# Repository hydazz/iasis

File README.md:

# iasis

Iasis is a five-port USB-C hub for restoring Apple devices. It can put Macs into DFU mode without the keyboard sequence. The host runs the restores on macOS, Linux or Windows. The same ports connect ordinary USB peripherals.

The hardware is a prototype.

## Hardware

The main board has a USB-C power input and a charging supply for each target port. A power supply on that input runs the hub and charges the targets. Without one, the host port runs the hub, and a USB-C host advertising 1.5 A or 3 A also powers the targets.

The optional [CM5 carrier](hardware/boards/cm5/README.md) plugs into the main board and houses a Compute Module 5, NVMe storage and Ethernet. The [printed case](hardware/case/README.md) holds the main board alone or with the carrier, with plain or OLED lids.

See the [main board](hardware/boards/iasis/README.md) for fabrication files and ordering settings.

## Software

| Part                                    | Role                                       |
| --------------------------------------- | ------------------------------------------ |
| [IasisOS](crates/firmware/README.md)    | Firmware on the hub's RP2354               |
| [`iasisd`](#host-agent)                 | Host agent: follows hubs and runs restores |
| `iasis`                                 | Command-line control of hubs and the agent |
| [Iasis for macOS](apps/macos/README.md) | Menu bar app, with the host tools inside   |

They share one version and are released together.

## Build

Install [mise](https://mise.jdx.dev/) and, for hardware work, KiCad 10 with its standard libraries. Run from the repository root:

```sh
mise install
mise run deps
mise run host:build
```

The host tools are `target/release/iasis` for hub control and `target/release/iasisd`, the [host agent](#host-agent). Keep `iasis-gateway` beside both. The agent needs read/write access to the management USB device. On Linux, the [Debian package](crates/iasis/README.md#debian-package) installs them with that access, and on Windows the [installer](crates/iasis/README.md#windows-installer).

The build compiles the restore engine's C libraries from source. Install their build tools first: on macOS, the Xcode command line tools and `brew install autoconf automake libtool pkg-config cmake`; on Debian or Ubuntu, `build-essential git autoconf automake libtool pkg-config cmake libpcap-dev libusb-1.0-0-dev`; on Windows, `mise bootstrap` (MSYS2 and its MINGW64 packages) with rustup's default host set to `x86_64-pc-windows-gnu`, building from MSYS2's MINGW64 shell.

| Task               | Output                                                            |
| ------------------ | ----------------------------------------------------------------- |
| `mise run build`   | Host tools, IasisOS, case STLs, board STEPs and fabrication files |
| `mise run lint`    | Rust, Python, workflow and KiCad checks                           |
| `mise run test`    | Software, placement-conversion and case-fit tests                 |
| `mise run preview` | Board and case images                                             |
| `mise run format`  | Formatted sources and configuration                               |

Builds, checks and previews are separate tasks. Python tools share the root `.venv`; `mise install` also installs the Lefthook hooks.

## Use

Connect the host and charged targets. Ports are numbered 1–5, starting at the dot on the case.

```sh
target/release/iasis
target/release/iasis list
target/release/iasis --serial 0123456789abcdef rename "Bench A"
target/release/iasis --hub "Bench A" dfu 1
target/release/iasis --hub "Bench A" ports --watch
```

`iasis` alone lists every hub and its ports; `iasis watch` keeps the list current. It works through the [host agent](#host-agent), which must be running. With one hub attached, commands act on it; with several, select one by name or by the serial from `iasis list`. Names match without case, can contain spaces and punctuation, and fit the OLED’s 16 printable ASCII characters. If two hubs share a name, select by serial. An empty name clears the label. Use `ports --watch` to see the USB mode, identity and link (none, USB 2 or USB 3) on each port. If a Mac acknowledges the DFU request and then disappears from USB, check the data cable and the Mac’s [DFU socket](https://support.apple.com/en-us/120694). A locked Mac laptop withholds USB data from an accessory it has not allowed until someone unlocks it and allows it ([Apple](https://support.apple.com/en-us/102282)); until then its port shows power and no link, and DFU still works.

The button selects targets with a tap and acts on them with a hold, with or without an OLED.

| Button           | Status light | Result                                                |
| ---------------- | ------------ | ----------------------------------------------------- |
| Tap              |              | Select All, then each attached port in turn           |
| Hold and release | Blue         | DFU                                                   |
|                  | Amber        | Reboot                                                |
|                  | Purple       | Ask the waiting host to prepare a [restore](#restore) |
| Keep holding     | Normal       | Nothing is sent                                       |

A hold steps through the actions the selected targets take, in this order: the first after half a second, each next one 1.5 seconds later. DFU and Reboot are offered only where a target lists them, and DFU only on a port that carries the target's DFU USB. On a Mac that is its DFU port; its other ports take Reboot.

Port lights outside the selection dim. While the button is held, only the ports the action will reach stay bright. An emptied port stays selected for 30 seconds so a replacement target takes its place.

After a DFU the port pulses blue. It turns steady blue once a host sees the target in DFU, which needs the [host agent](#host-agent). The [light table](crates/firmware/README.md#controls-and-status) lists every colour.

A steady white port light marks a device Iasis cannot act on, such as a USB peripheral or a laptop. It can use USB normally. DFU leaves target data intact and works with Apple Configurator. `power <port> off` disables a port. `power <port> on` enables it and retries a fault. The selected hub stores its name and light brightness in flash.

With Default USB power, including an A-to-C cable, the target ports stay off until a power supply is connected. A USB-C host advertising 1.5 A or 3 A can power the ports directly. They share the available current. Connect external power if the targets draw more during recovery. See the [firmware power table](crates/firmware/README.md#port-power) for the limits.

### Host agent

`iasisd` attends every connected hub and needs no arguments:

```sh
target/release/iasisd
```

While the agent is running:

- It tells each hub which USB mode its targets are in, so a port light turns steady blue when its target really is in DFU, however it got there.
- It keeps the [restore images](#images) and fetches the ones it lacks.
- It runs the restores that a hub's button or a client asks for.
- On Linux and macOS, it can share an internet connection with attached devices over USB.

The status light is green and the OLED shows a USB symbol while a host is attached. One host holds a hub at a time, and on it only the agent opens the hub; `iasis` and the Mac app are its clients, and other clients use its [local socket](crates/api/README.md). Without the agent, `iasis` says how to start it.

On Linux, the [Debian package](crates/iasis/README.md#debian-package) runs the agent at boot for the person signed in at the computer and members of the `iasis` group. On Windows, the [installer](crates/iasis/README.md#windows-installer) runs it at boot for Administrators and the person signed in at the computer. On macOS, the [menu bar app](apps/macos/README.md) shows the same hubs and ports, sends the same actions and runs the agent it carries while you are logged in. To run your own build in the background, turn Iasis off under Background App Activity in Login Items & Extensions, then prefix the command with `launchctl submit -l local.iasisd --`. With `IASIS_HOME` set to a directory, the agent keeps its files and socket there, and `iasis` with the same `IASIS_HOME` talks to it.

### USB Internet Sharing

On Linux or macOS, use the CLI. The Mac app also has **Share internet over USB** in Settings > General.

```sh
iasis sharing on
iasis sharing       # show the setting and ports being served
iasis sharing off
```

A directly attached Apple device that offers USB Ethernet can use the host’s internet connection over its charging and restore cable. Sharing follows the host’s routing and resumes when a device restarts. The OLED shows a network symbol while the agent serves at least one port on that hub.

On Linux, a Mac is served once the kernel’s `cdc_ncm` driver lists its USB ID: from Linux 7.2 for the M5 MacBook Air (`linux-oem-26.04b` on Ubuntu 26.04) and 7.4 for the M1 MacBook Air. iPhones and iPads won’t be served until Debian and Ubuntu ship a usbmuxd newer than 1.1.1.

Windows can't share: Microsoft's NCM driver fails on a Mac's USB Ethernet, and Apple's Windows driver keeps iPhones and iPads from offering theirs.

A Mac with no USB device of its own while it runs, such as the MacBook Neo, reaches the host only through Apple Debug USB. The agent turns it on when such a Mac's port shows nothing on USB, and a DFU or restore through Iasis keeps it on into the restored system. macOS and the Linux agent present the Mac behind it, Linux without `cdc_ncm`, while the Mac is awake.

Setup Assistant can use this connection for Automated Device Enrollment. See the [Mac app guide](apps/macos/README.md#usb-internet-sharing) for host permissions.

### Images

The agent holds IPSW archives. One archive restores every model its manifest names: a macOS image restores every Mac that release supports, and an iPadOS or iOS image a few related models. Archives for different models can share a version and build number.

A restore asks what Apple signs for each device before it chooses an image:

- With no image that fits, it downloads the newest release.
- With an image that is the newest release, or newer, it uses it.
- With an older image Apple still signs, it uses that one, or downloads the newest with `--latest`. The Mac app asks which.
- An image Apple no longer signs is deleted and the newest release downloaded. Apple signs older macOS releases for a long time and older iOS and iPadOS releases only briefly.
- When the catalog cannot be reached, the newest image that fits is used.

Any release Apple signs can also be downloaded ahead of time. Release listings come from [ipsw.me](https://ipsw.me) and the archives from Apple's servers, checked against their published SHA-256.

```sh
target/release/iasis images                           # each image by name, and any download
target/release/iasis images releases Macmini9,1       # the releases Apple signs for a model
target/release/iasis images fetch Macmini9,1          # download the newest of them
target/release/iasis images fetch Macmini9,1 --build 25G80
target/release/iasis images add /path/to/UniversalMac.ipsw
target/release/iasis images remove UniversalMac_27.2.1_26B131_Restore.ipsw
```

An image stays until it is removed. Removing one that is still downloading stops the download, and removing one a restore is reading takes it out when that restore ends, unless a restore or `images fetch` asks for its release first. A download goes on while a restore waits for it or after `images fetch`; one that no restore waits for any longer stops. An image added from a file is never taken for an unsigned one, since the catalog may not list it. Downloaded images live in the agent's cache directory, `~/Library/Caches/com.hydaz.Iasis` on macOS and `/var/cache/iasis` on Linux, which the system may clear; the agent then downloads an image again when a restore needs it. Images added from a file live in its state directory, `~/Library/Application Support/com.hydaz.Iasis` on macOS and `/var/lib/iasis` on Linux. On macOS, a release Finder has already downloaded to `~/Library/iTunes` is cloned from there instead, once its SHA-256 matches. `images add` sends the archive to the agent, which keeps it once every member's checksum matches. The agent owns both directories: when it starts, it lists any archive it finds there that it did not, once every member's checksum matches, and deletes one that does not. A Mac image is about 26 GB and an iPad image about 11 GB.

While an image is being fetched for a target, its port pulses purple, the OLED labels it `IMG`, and `iasis` shows the percentage.

### Restore

Restores are built into the host tools through [RestoreKit](https://github.com/fcjr/restorekit), for targets in ordinary DFU and Apple Debug USB DFU. On Linux they go through the system usbmuxd. An iPhone or iPad the hub can't signal into DFU, such as one on a Lightning cable, restarts into recovery mode at the host's request and restores from there. It must trust the host: unlock it and tap Trust when it asks, unless its enrollment profile lists the host's [supervision certificate](#supervised-iphones-and-ipads).

```sh
target/release/iasis --serial 0123456789abcdef restore --ports 1,2,3,4,5 --erase
```

**`--erase` erases the selected targets.** The agent runs the restore, and the command follows each port and prints its result as soon as that port ends. The [image store](#images) supplies each target's image.

Each target is its own job, and each restore its own process. A job fetches the target's image before it puts the target into DFU or recovery when this host already knows the target's model; otherwise the target waits there for it. A restore that fails while its target is still in DFU or recovery is started again, up to three times. A target that can’t be prepared, such as an iPad waiting for Trust, ends with the reason on its port while the others restore.

Erased Macs restart into Setup Assistant. Add `--shutdown-macs` to a restore command to power them off after that erase. Revived devices always restart.

To advance Setup Assistant on iPhones and iPads, supply the language and regional format. Add `--enroll` to request Automated Device Enrollment.

```sh
iasis advance-setup --ports 1,2 --language en-AU --locale en_AU
iasis advance-setup --ports 1,2 --language en-AU --locale en_AU --enroll
```

The same options on `iasis restore --erase` run setup after installation. Each device keeps any language or region it has already accepted. The CLI prints the result for each port.

In the Mac app, choose the language, region and enrollment preference in **Settings > Restore**. **Advance Setup** applies them immediately. **Advance Setup After Erase** also applies them to erases started from the app or the hub button.

Advance Setup activates the device if needed. With enrollment enabled, it then requests the assigned management profile. The host needs internet access for activation. The device reaches its enrollment service over Wi-Fi or USB Internet Sharing. If the result says “continue on device”, follow the sign-in or management prompt in Setup Assistant. A “Partially Set Up” prompt also needs a choice on the device.

The host stays out of idle sleep from a target's preparation until its restore ends, while its display can still sleep. On battery, a Windows laptop with Modern Standby drops that hold five minutes after its sleep timeout.

The device inspector shows the requested steps and keeps each outcome. During installation, the restore row shows the current activity, an overall progress bar and an approximate countdown.

Logs and working files go under `restores/` in the agent's cache directory. Allow space for an extracted OS image per worker. Iasis matches each image to the target's chip and board IDs, or to its product type when only a model identifier is available. The restore program checks Apple signing.

On macOS 27.3, Finder opens a window for each Mac, iPad or iPhone that enters DFU or recovery mode. To stop it, turn off **Open Finder for DFU and Recovery** in the app's Settings > General, or run this once as the user running Finder. The preference is undocumented.

```sh
defaults write com.apple.AMPDeviceDiscoveryAgent reveal-devices -bool false
```

To restore the default behaviour, run `defaults delete com.apple.AMPDeviceDiscoveryAgent reveal-devices`.

#### Supervised iPhones and iPads

An iPhone or iPad whose enrollment profile lists the agent's supervision certificate pairs with the host without asking for Trust, so its restores through recovery need no one at the device. Other devices still ask.

The agent makes its identity when it first starts. Export the certificate with Export… in the identity's ⋯ menu, in the Mac app's Settings > Restore, or with `iasis supervision certificate Iasis.cer`, and add it to the devices' Automated Device Enrollment profile as a supervising host certificate. In Intune that is Sync with computers, Allow Apple Configurator by certificate, in the enrollment program token's profile. A device takes the certificate when it enrolls, so an enrolled one needs one erase, with a Trust tap, and enrollment again first.

To back the identity up or give another host the same one, export it with its private key in a password-protected PKCS #12 archive, with Export… in the Mac app or `iasis supervision export Iasis.p12`, and import it with Import… or `iasis supervision import Iasis.p12`. The agent keeps it as `supervision.pem` in its state directory, open to the agent's account alone: mode 600 in a 700 directory on macOS (`~/Library/Application Support/com.hydaz.Iasis`) and Linux (`/var/lib/iasis`), and on Windows an access list of the agent's account and Administrators. Anyone holding the identity can pair with every device that lists its certificate.

#### Button restores

The hub's Restore hold needs only the agent. Tap to select targets, then hold until the status light turns purple and release. Preparation fetches any image the agent lacks and puts the targets into DFU or recovery. Once every target that could be prepared is ready, the status light blinks purple: hold for three seconds to confirm, or tap to cancel. The agent keeps listening after cancellation and while workers run.

An erase stays ready for 20 seconds. If it lapses, make the Restore hold again: the images are in the store by then.

#### Example restore times

These Rev A timings use cached macOS 27 IPSWs. The single-Mac column times the restore worker. The five-Mac column times the whole command on one hub, including preparation.

| Target | Image transfer | Restore worker                               |       One Mac | Five together |
| ------ | -------------- | -------------------------------------------- | ------------: | ------------: |
| M1 Air | USB 2          | idevicerestore                               |       15m 06s |       58m 14s |
| M1 Air | USB 2          | idevicerestore, experimental binary FileData |       12m 36s |       47m 57s |
| M5 Air | USB 3, 10 Gb/s | RestoreKit                                   | 3m 59s–4m 21s |             — |

The five M1s shared a 480 Mb/s uplink and reached 45 MB/s combined. Across two hubs, ten jobs overlapped for 4m 52s and at least eight Macs transferred data together.

Use USB 2 as a planning estimate for M1–M3 and USB 3 for M4 or newer Macs with a SuperSpeed restore link. Five-Mac USB 3 time is unmeasured.

| Other benches                                       |                                                                   Reported batch time |
| --------------------------------------------------- | ------------------------------------------------------------------------------------: |
| University of Utah, ten MacBooks on Acroname hubs   |           [35–40 min](https://apple.lib.utah.edu/macbook-imaging-automation-journey/) |
| Twocanoes, fifteen Macs on its USB 3 restore system | [Under 10 min](https://tperfitt.twocanoes.com/2026/04/19/dfu-restore-for-mac-is.html) |

### Revive

Revive repairs a device and keeps its data: a Mac gets its firmware and recoveryOS reinstalled, an iPhone or iPad its system. It installs the image a restore would and enters DFU or recovery the same way.

```sh
target/release/iasis --serial 0123456789abcdef revive --ports 2
```

A revived Mac can start in recoveryOS and ask for an administrator's password before macOS starts.

## IasisOS and protocol

`iasis --hub "Bench A" update` writes the IasisOS that the host tools carry, so a hub and its host run the same release. The hub leaves USB for a few seconds and its ports lose power. [Build, update and recover IasisOS](crates/firmware/README.md) through the same host USB connection. The [protocol README](crates/protocol/README.md) describes the management interface for host applications.

## License

Original code, firmware, CAD, documentation and enclosure files are [Apache-2.0](LICENSE). Third-party assets retain their own licences and notices.

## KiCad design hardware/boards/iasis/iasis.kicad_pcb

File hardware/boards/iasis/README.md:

# Iasis board

The main board connects five target USB-C ports to a host and controls their power and DFU signalling. It has a USB-C power input, a charging supply for each port and a socket for the optional [CM5 carrier](../cm5/README.md).

## Fabrication files

Install the [development tools](../../../README.md#build), including KiCad 10 and its standard libraries, then run from the repository root:

```sh
mise run //hardware/boards/iasis:lint
mise run //hardware/boards/iasis:fab
```

Outputs go to `build/boards/iasis/`. Both populations use the same `gerbers.zip`:

| Population | Assembly files                   | Includes                                                    |
| ---------- | -------------------------------- | ----------------------------------------------------------- |
| Default    | `bom.csv`, `cpl.csv`             | Every part, including the CM5 socket and its protected feed |
| NoCM5      | `bom-NoCM5.csv`, `cpl-NoCM5.csv` | Every part except the CM5 socket and its feed               |

The CM5 build uses the default population plus the separate carrier.

## JLCPCB order

| Setting           | Value                                         |
| ----------------- | --------------------------------------------- |
| Layers / size     | 6 / 133 × 102 mm                              |
| Thickness         | 1.6 mm; stackup finished thickness 1.54 mm    |
| Stackup           | `JLC06161H-3313`                              |
| Colour / finish   | Green / ENIG                                  |
| Via covering      | Epoxy filled and capped                       |
| Minimum via hole  | 0.3 mm                                        |
| Impedance control | No requirement                                |
| PCB mark          | Remove mark                                   |
| Assembly          | Economic PCBA, top side, JLCPCB tooling holes |
| Parts             | Customer-selected                             |

Keep green, ENIG and 1.6 mm for the six-layer [Economic assembly combination](https://jlcpcb.com/capabilities/pcb-assembly-capabilities). The USB pairs use the specified stackup; do not substitute another one.

Upload `gerbers.zip` and the matching BOM/CPL pair. Before ordering:

1. Select the USB-C connector rows (`J1001`, `J401–J901`); they can be left unchecked after upload.
2. Check part matches, stock and Economic eligibility. Replace unsuitable parts in the schematic and regenerate the exports.
3. Inspect **Component Placements**, including polarity and connector orientation. If **Align** moves a part off its pads, fix the [placement correction](../../tools/README.md#placement-corrections) and export again.
4. Enable **Confirm Parts Placement** and disable automatic confirmation.

## Design files and revisions

Open `iasis.kicad_pro` in KiCad. Shared symbols, footprints and models are in `../../shared`, with their licence notices.

Use `mise run //hardware/boards/iasis:step` for the populated STEP and `:preview` for `board.png`. The [board tools](../../tools/README.md) describe the exports and checks.

`version.txt` holds the board's version, which the title blocks and the underside silkscreen print. Both populations share it. Each ordered version is a release tagged `iasis-board-v<version>` with its `gerbers.zip`, BOM and placement files attached. Revision A, the first order, is version 1.0.0; its files are in the `iasis-rev-a` release. Software versions are separate.

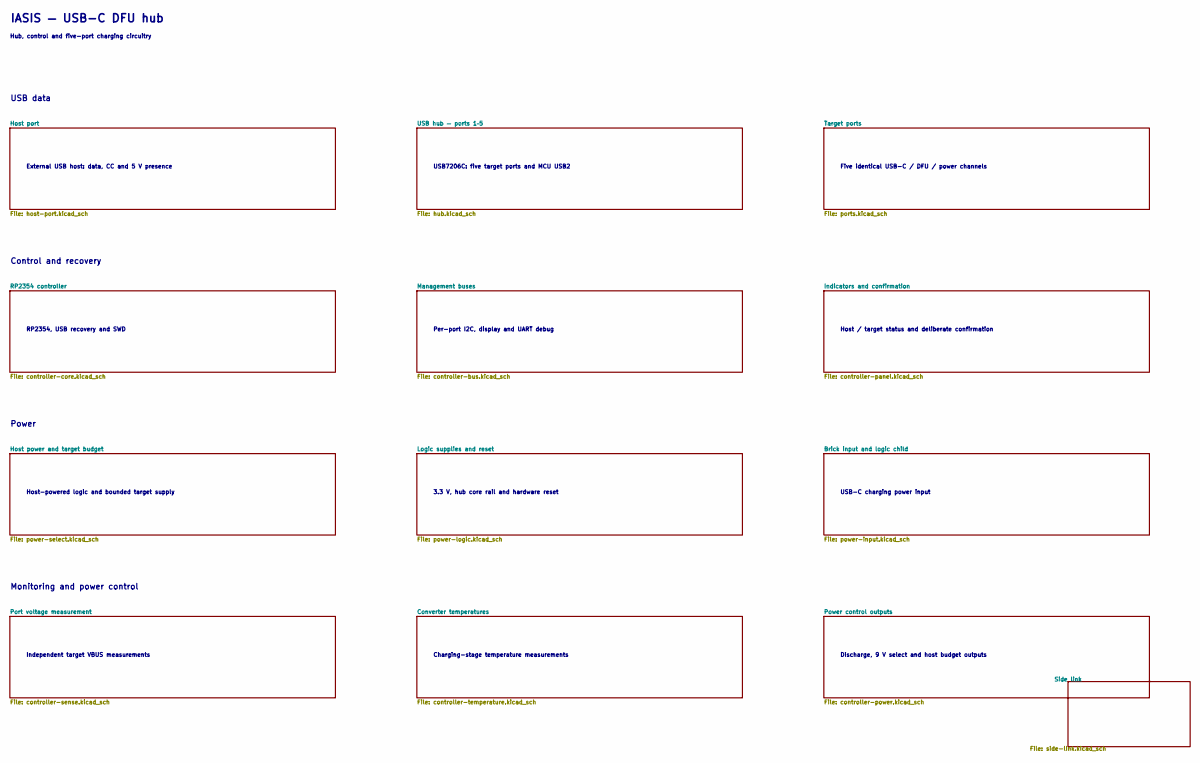
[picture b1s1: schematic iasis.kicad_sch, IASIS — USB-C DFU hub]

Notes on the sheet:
Power
RP2354, USB recovery and SWD
Host / target status and deliberate confirmation
IASIS — USB-C DFU hub
Hub, control and five-port charging circuitry
Independent target VBUS measurements
3.3 V, hub core rail and hardware reset
External USB host: data, CC and 5 V presence
Per-port I2C, display and UART debug
Host-powered logic and bounded target supply
Control and recovery
Five identical USB-C / DFU / power channels
USB7206C: five target ports and MCU USB2
Charging-stage temperature measurements
Monitoring and power control
USB-C charging power input
Discharge, 9 V select and host budget outputs
USB data

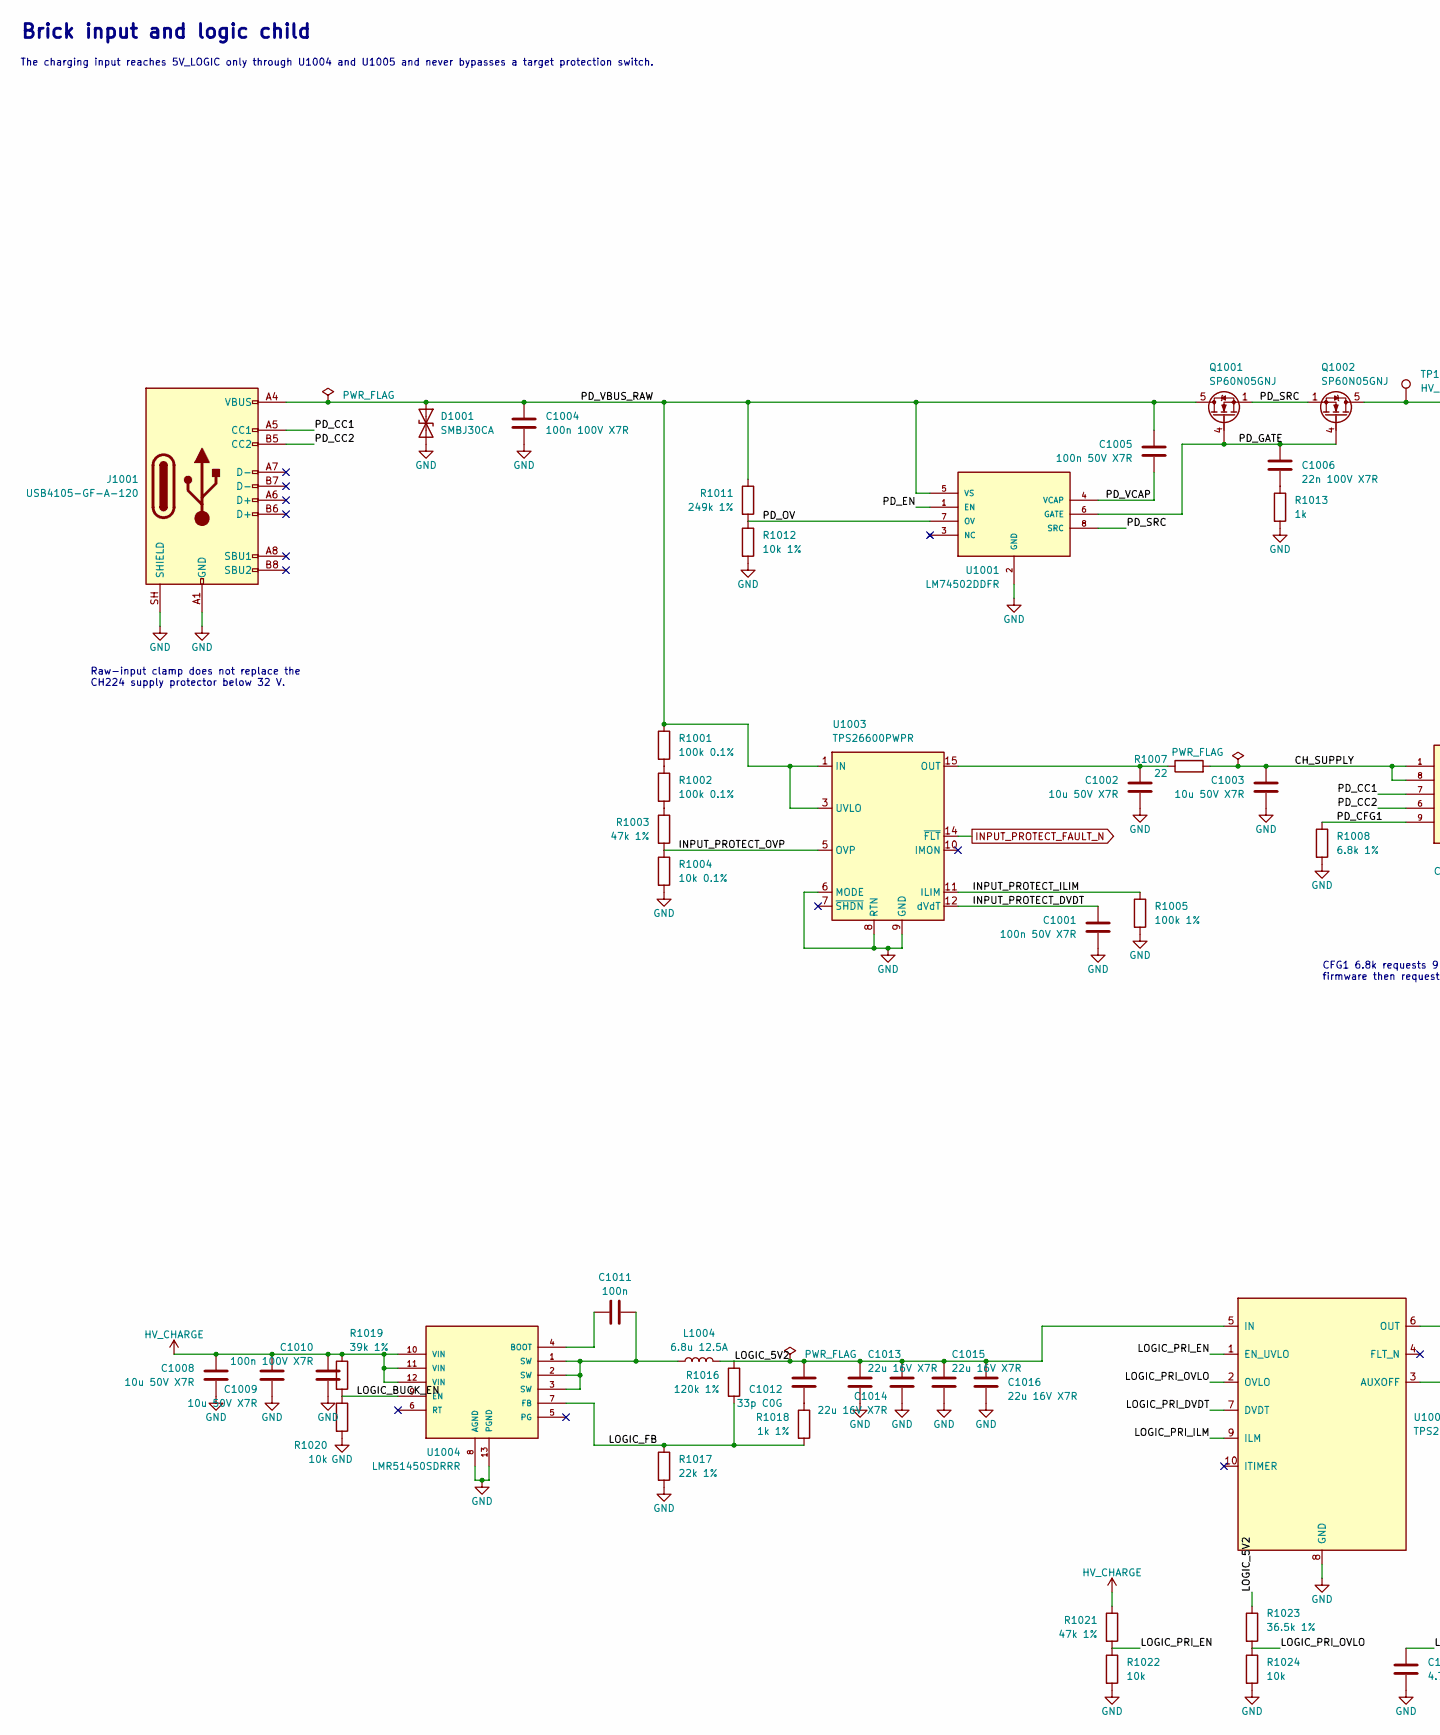
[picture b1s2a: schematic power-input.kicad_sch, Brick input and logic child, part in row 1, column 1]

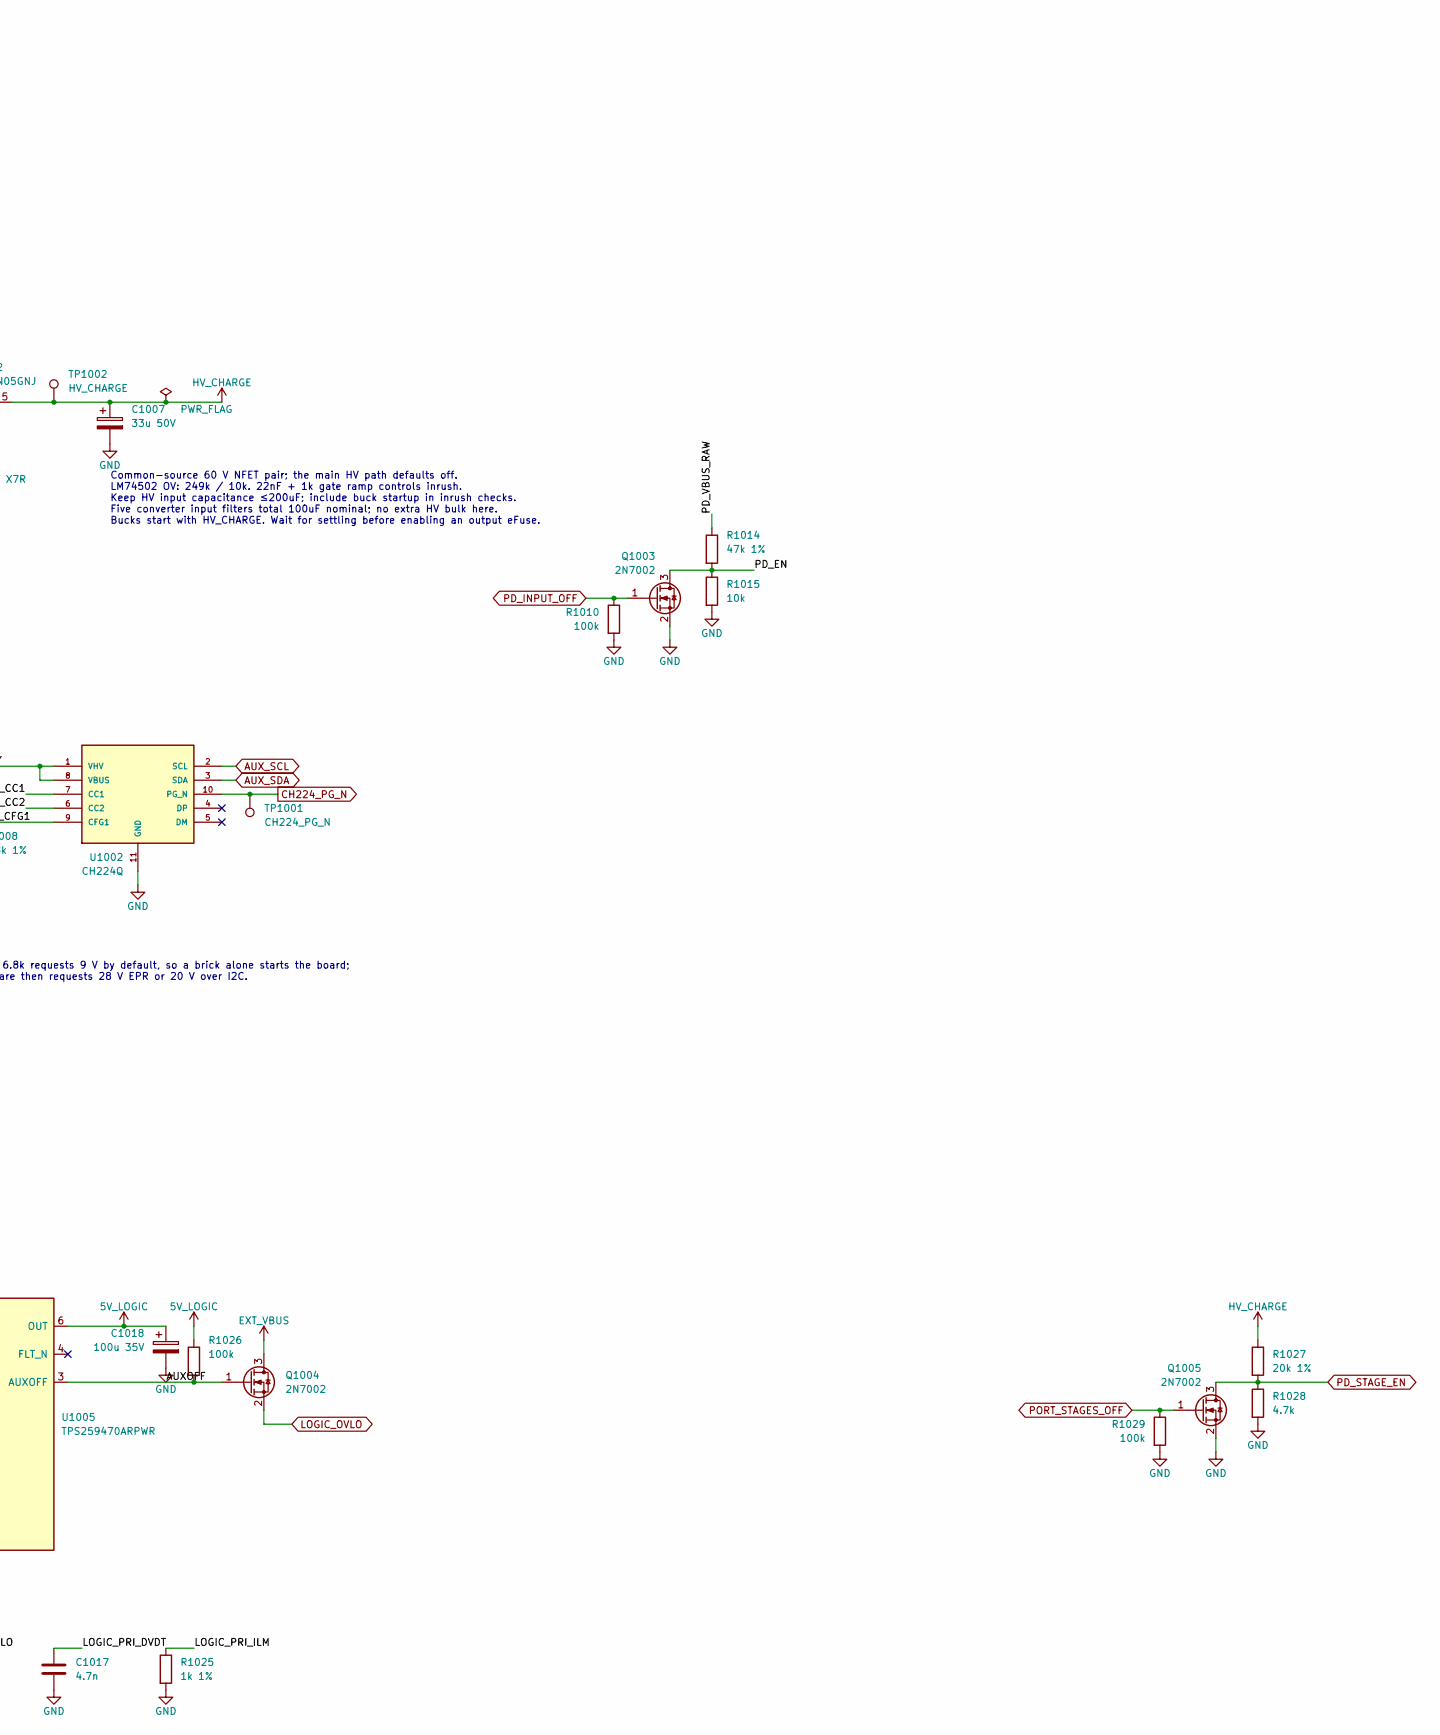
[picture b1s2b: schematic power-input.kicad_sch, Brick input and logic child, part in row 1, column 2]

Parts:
C1001, C1005: 100n 50V X7R; C_0402_1005Metric; MPN CL05B104KB54PNC; LCSC C307331
C1002, C1003, C1008, C1009: 10u 50V X7R; C_1210_3225Metric; MPN CL32B106KBJNNNE; LCSC C138687
C1004, C1010: 100n 100V X7R; C_0603_1608Metric; MPN CC0603KRX7R0BB104; LCSC C113803
C1006: 22n 100V X7R; C_0603_1608Metric; MPN CC0603KRX7R0BB223; LCSC C313105
C1007: 33u 50V; CP_Elec_6.3x7.7; MPN EEHZA1H330XP; LCSC C178637
C1011: 100n; C_0402_1005Metric; MPN CL05B104KO5NNNC; LCSC C1525
C1012: 33p C0G; C_0402_1005Metric; MPN 0402CG330J500NT; LCSC C1562
C1013, C1014, C1015, C1016: 22u 16V X7R; C_1210_3225Metric; MPN CL32B226KOJNNNE; LCSC C55530
C1017: 4.7n; C_0402_1005Metric; MPN 0402B472K500NT; LCSC C1538
C1018: 100u 35V; CP_Elec_6.3x7.7; MPN HBO101M1VTR-0608; LCSC C3031628
D1001: SMBJ30CA; D_SMB; MPN SMBJ30CA; LCSC C83847
J1001: USB4105-GF-A-120; GCT_USB4105_GF_A_120; MPN USB4105-GF-A-120; LCSC C5184243
L1004: 6.8u 12.5A; PSTMAA666460; MPN PSTMAA666460-6R8MB; LCSC C55172548
Q1001, Q1002: SP60N05GNJ; Vishay_PowerPAK_1212-8_Single; MPN SP60N05GNJ; LCSC C22466768
Q1003, Q1004, Q1005: 2N7002; SOT-23; MPN 2N7002; LCSC C8545
R1001, R1002: 100k 0.1%; R_0603_1608Metric; MPN RT0603BRD07100KL; LCSC C122538
R1003, R1014, R1021: 47k 1%; R_0402_1005Metric; MPN 0402WGF4702TCE; LCSC C25792
R1004: 10k 0.1%; R_0603_1608Metric; MPN RT0603BRD0710KL; LCSC C95204
R1005: 100k 1%; R_0402_1005Metric; MPN 0402WGF1003TCE; LCSC C25741
R1007: 22; R_0603_1608Metric; MPN 0603WAF220JT5E; LCSC C23345
R1008: 6.8k 1%; R_0402_1005Metric; MPN 0402WGF6801TCE; LCSC C25917
R1010, R1026, R1029: 100k; R_0402_1005Metric; MPN 0402WGF1003TCE; LCSC C25741
R1011: 249k 1%; R_0402_1005Metric; MPN 0402WGF2493TCE; LCSC C11425
R1012: 10k 1%; R_0402_1005Metric; MPN 0402WGF1002TCE; LCSC C25744
R1013: 1k; R_0402_1005Metric; MPN 0402WGF1001TCE; LCSC C11702
R1015, R1020, R1022, R1024: 10k; R_0402_1005Metric; MPN 0402WGF1002TCE; LCSC C25744
R1016: 120k 1%; R_0402_1005Metric; MPN 0402WGF1203TCE; LCSC C25750
R1017: 22k 1%; R_0402_1005Metric; MPN 0402WGF2202TCE; LCSC C25768
R1018, R1025: 1k 1%; R_0402_1005Metric; MPN 0402WGF1001TCE; LCSC C11702
R1019: 39k 1%; R_0402_1005Metric; MPN 0402WGF3902TCE; LCSC C25783
R1023: 36.5k 1%; R_0402_1005Metric; MPN 0402WGF3652TCE; LCSC C25887
R1027: 20k 1%; R_0402_1005Metric; MPN 0402WGF2002TCE; LCSC C25765
R1028: 4.7k; R_0402_1005Metric; MPN 0402WGF4701TCE; LCSC C25900
TP1001: CH224_PG_N; TestPoint_Pad_D1.0mm
TP1002: HV_CHARGE; TestPoint_Pad_D1.0mm
U1001: LM74502DDFR; Texas_DDF0008A_SOT-8_1.6x2.9mm_P0.65mm; MPN LM74502DDFR; LCSC C3236215
U1002: CH224Q; Texas_DSQ0010A_WSON-10-1EP_2x2mm_P0.4mm_EP0.9x1.5mm; MPN CH224Q; LCSC C46061833
U1003: TPS26600PWPR; HTSSOP-16-1EP_4.4x5mm_P0.65mm_EP3.4x5mm_Mask2.66x2.46mm_The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; MPN TPS26600PWPR; LCSC C544399
U1004: LMR51450SDRRR; TI_DRR0012G; MPN LMR51450SDRRR; LCSC C6890985
U1005: TPS259470ARPWR; TI_RPW0010A; MPN TPS259470ARPWR; LCSC C3662799

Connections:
5V_LOGIC: C1018.1, R1026.1, U1005.6 (OUT); also elsewhere on the board
/Brick input and logic child/AUXOFF: Q1004.1 (G), R1026.2, U1005.3 (AUXOFF)
/Brick input and logic child/CH_SUPPLY: C1003.1, R1007.2, U1002.1 (VHV), U1002.8 (VBUS)
/Brick input and logic child/INPUT_PROTECT_DVDT: C1001.1, U1003.12 (dVdT)
/Brick input and logic child/INPUT_PROTECT_ILIM: R1005.1, U1003.11 (ILIM)
/Brick input and logic child/INPUT_PROTECT_OVP: R1003.2, R1004.1, U1003.5 (OVP)
/Brick input and logic child/LOGIC_5V2: C1012.1, C1013.1, C1014.1, C1015.1, C1016.1, L1004.2, R1016.1, R1023.1, U1005.5 (IN)
/Brick input and logic child/LOGIC_BUCK_EN: R1019.2, R1020.1, U1004.9 (EN)
/Brick input and logic child/LOGIC_FB: R1016.2, R1017.1, R1018.2, U1004.7 (FB)
/Brick input and logic child/LOGIC_PRI_DVDT: C1017.1, U1005.7 (DVDT)
/Brick input and logic child/LOGIC_PRI_EN: R1021.2, R1022.1, U1005.1 (EN_UVLO)
/Brick input and logic child/LOGIC_PRI_ILM: R1025.1, U1005.9 (ILM)
/Brick input and logic child/LOGIC_PRI_OVLO: R1023.2, R1024.1, U1005.2 (OVLO)
/Brick input and logic child/PD_CC1: J1001.A5 (CC1), U1002.7 (CC1)
/Brick input and logic child/PD_CC2: J1001.B5 (CC2), U1002.6 (CC2)
/Brick input and logic child/PD_CFG1: R1008.1, U1002.9 (CFG1)
/Brick input and logic child/PD_EN: Q1003.3 (D), R1014.2, R1015.1, U1001.1 (EN)
/Brick input and logic child/PD_GATE: C1006.1, Q1001.4 (G), Q1002.4 (G), U1001.6 (GATE)
/Brick input and logic child/PD_OV: R1011.2, R1012.1, U1001.7 (OV)
/Brick input and logic child/PD_SRC: Q1001.1 (S), Q1001.2 (S), Q1001.3 (S), Q1002.1 (S), Q1002.2 (S), Q1002.3 (S), U1001.8 (SRC)
/Brick input and logic child/PD_VBUS_RAW: C1004.1, C1005.2, D1001.1 (A1), J1001.A4 (VBUS), J1001.A9 (VBUS), J1001.B4 (VBUS), J1001.B9 (VBUS), Q1001.5 (D), R1001.1, R1011.1, R1014.1, U1001.5 (VS), U1003.1 (IN), U1003.2 (IN), U1003.3 (UVLO)
/Brick input and logic child/PD_VCAP: C1005.1, U1001.4 (VCAP)
AUX_SCL: U1002.2 (SCL); also elsewhere on the board
AUX_SDA: U1002.3 (SDA); also elsewhere on the board
CH224_PG_N: TP1001.1 (1_1), U1002.10 (PG_N); also elsewhere on the board
EXT_VBUS: Q1004.3 (D); also elsewhere on the board
GND: C1001.2, C1002.2, C1003.2, C1004.2, C1007.2, C1008.2, C1009.2, C1010.2, C1013.2, C1014.2, C1015.2, C1016.2, C1017.2, C1018.2, D1001.2 (A2), J1001.A1 (GND), J1001.A12 (GND), J1001.B1 (GND), J1001.B12 (GND), J1001.SH (SHIELD), Q1003.2 (S), Q1005.2 (S), R1004.2, R1005.2, R1008.2, R1010.2, R1012.2, R1013.2, R1015.2, R1017.2, R1020.2, R1022.2, R1024.2, R1025.2, R1028.2, R1029.2, U1001.2 (GND), U1002.11 (GND), U1003.6 (MODE), U1003.8 (RTN), U1003.9 (GND), U1003.17 (RTN), U1004.8 (AGND), U1004.13 (PGND), U1005.8 (GND); also elsewhere on the board
HV_CHARGE: C1007.1, C1008.1, C1009.1, C1010.1, Q1002.5 (D), R1019.1, R1021.1, R1027.1, TP1002.1 (1_1), U1004.10 (VIN), U1004.11 (VIN), U1004.12 (VIN); also elsewhere on the board
INPUT_PROTECT_FAULT_N: U1003.14 (~FLT); also elsewhere on the board
LOGIC_OVLO: Q1004.2 (S); also elsewhere on the board
unnamed: C1002.1, R1007.1, U1003.15 (OUT), U1003.16 (OUT)
unnamed: C1006.2, R1013.1
unnamed: C1011.2, L1004.1, U1004.1 (SW), U1004.2 (SW), U1004.3 (SW)
unnamed: C1012.2, R1018.1
unnamed: R1001.2, R1002.1
unnamed: R1002.2, R1003.1
unnamed: C1011.1, U1004.4 (BOOT)
PD_INPUT_OFF: Q1003.1 (G), R1010.1; also elsewhere on the board
PD_STAGE_EN: Q1005.3 (D), R1027.2, R1028.1; also elsewhere on the board
PORT_STAGES_OFF: Q1005.1 (G), R1029.1; also elsewhere on the board

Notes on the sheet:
Common-source 60 V NFET pair; the main HV path defaults off. LM74502 OV: 249k / 10k. 22nF + 1k gate ramp controls inrush. Keep HV input capacitance ≤200uF; include buck startup in inrush checks. Five converter input filters total 100uF nominal; no extra HV bulk here. Bucks start with HV_CHARGE. Wai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
Brick input and logic child
CFG1 6.8k requests 9 V by default, so a brick alone starts the board; firmware then requests 28 V EPR or 20 V over I2C.
Raw-input clamp does not replace the CH224 supply protector below 32 V.
The charging input reaches 5V_LOGIC only through U1004 and U1005 and never bypasses a target protection switch.
